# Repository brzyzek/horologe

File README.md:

# horologe
A watch utilizing an ESP32 processor.

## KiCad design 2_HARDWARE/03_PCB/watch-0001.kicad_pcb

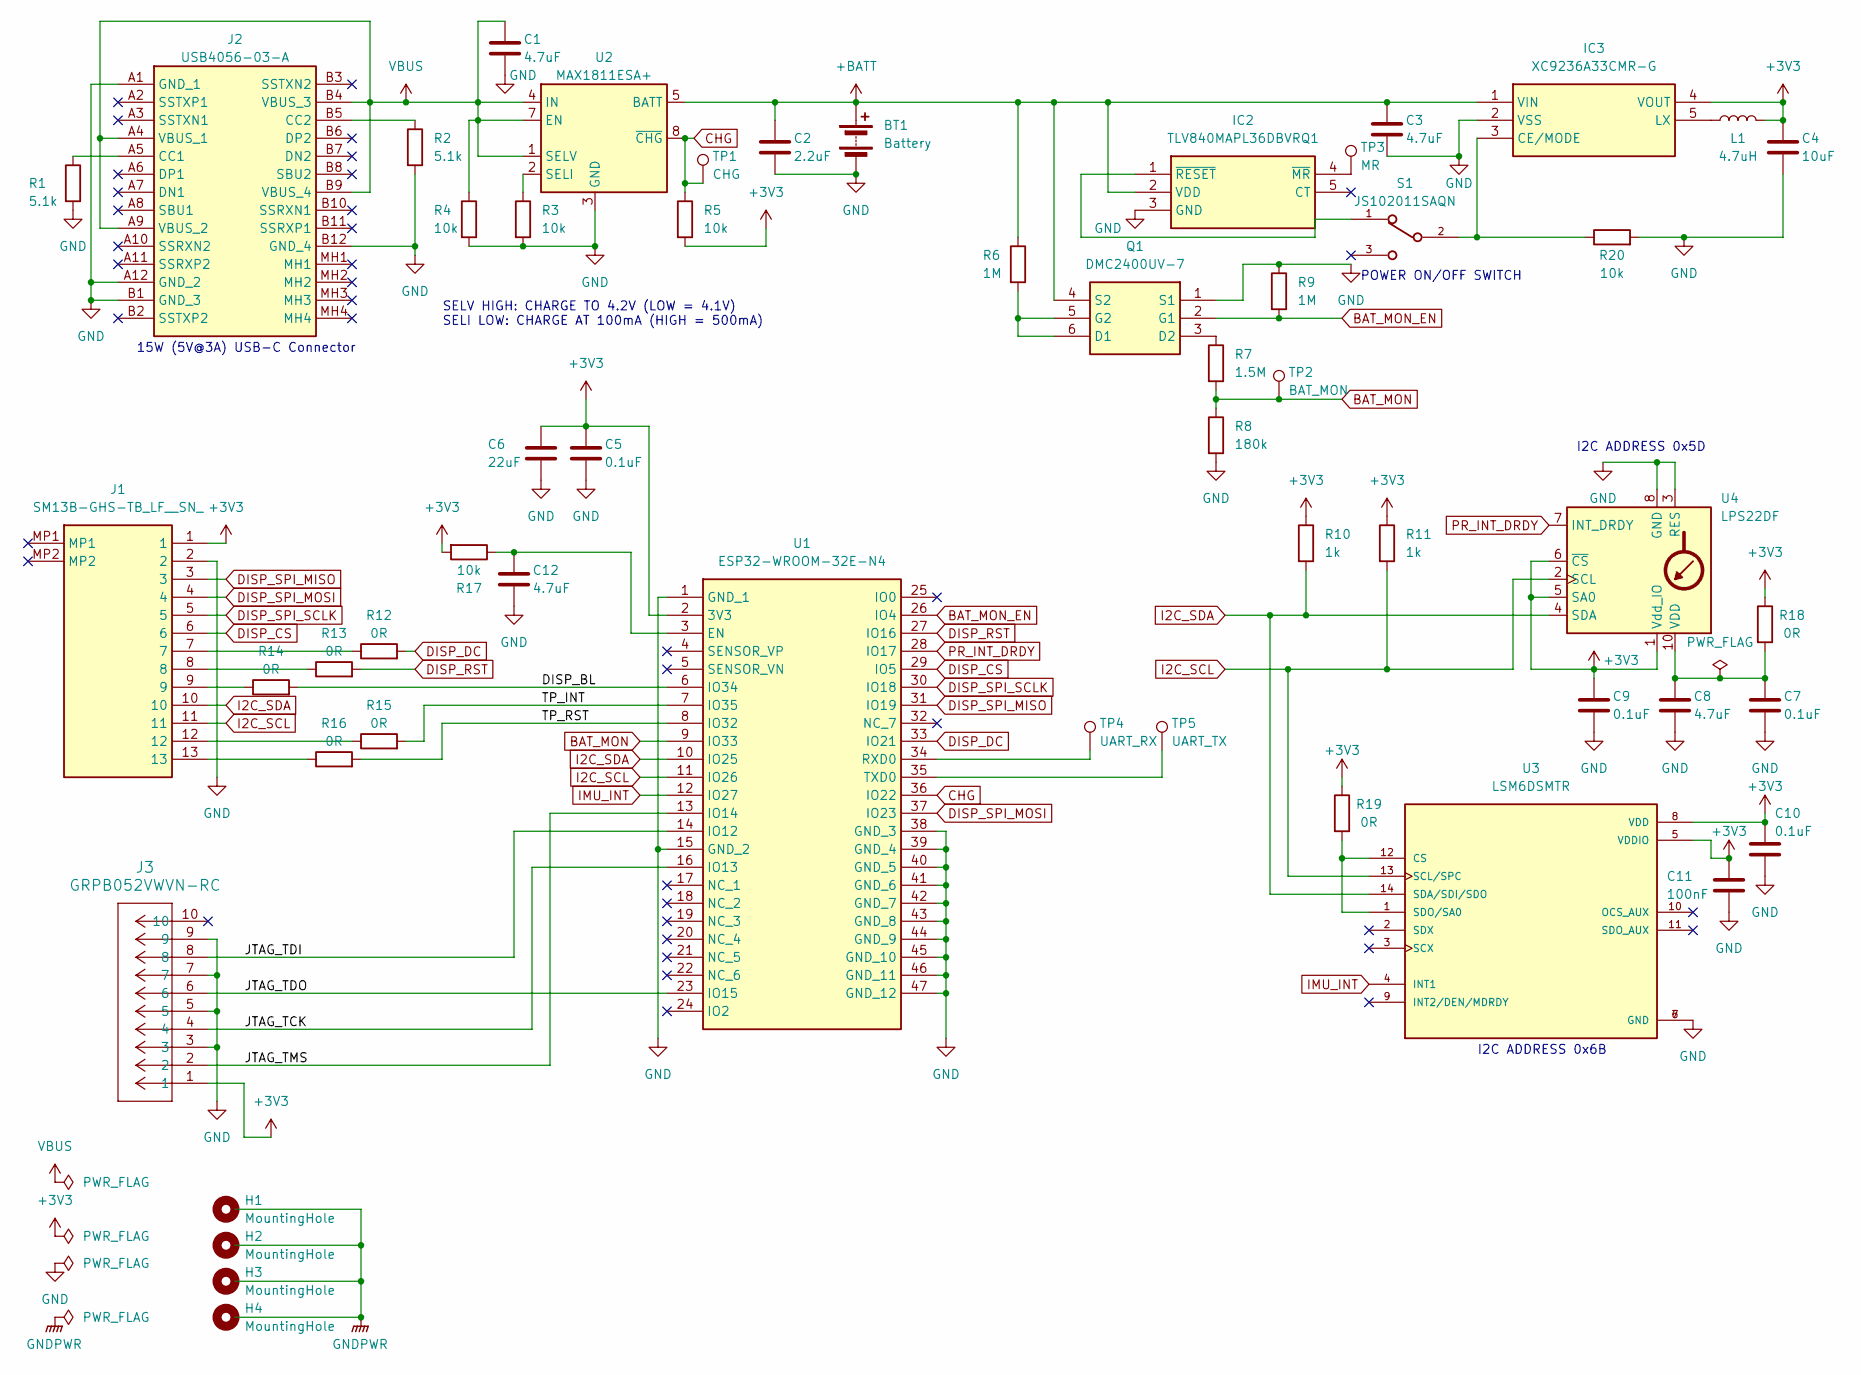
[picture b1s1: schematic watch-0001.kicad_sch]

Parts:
BT1: Battery; BAT_DUAL_1MM_TESTPOINTS
C1, C3, C8, C12: 4.7uF; C_0805_2012Metric
C2: 2.2uF; C_0805_2012Metric
C4: 10uF; C_0805_2012Metric
C5, C7, C9, C10: 0.1uF; C_0805_2012Metric
C6: 22uF; C_0805_2012Metric
C11: 100nF; C_0805_2012Metric
H1, H2, H3, H4: MountingHole; MountingHole_2.2mm_M2_DIN965_Pad
IC2: TLV840MAPL36DBVRQ1; SOT95P280X145-5N; Manufacturer_Part_Number TLV840MAPL36DBVRQ1; Mouser Part Number 595-V840MAPL36DBVRQ1
IC3: XC9236A33CMR-G; SOT95P280X130-5N; Manufacturer_Part_Number XC9236A33CMR-G; Mouser Part Number 865-XC9236A33CMR-G
J1: SM13B-GHS-TB_LF__SN_; SM13BGHSTBLFSN; Manufacturer_Part_Number SM13B-GHS-TB(LF)(SN)
J2: USB4056-03-A; USB405603A; Manufacturer_Part_Number USB4056-03-A; Mouser Part Number 640-USB4056-03-A
J3: GRPB052VWVN-RC; CONN_GRPB052VWVN-RC_SUL
L1: 4.7uH; IND_TAIYO_NR4018_TAY
Q1: DMC2400UV-7; SOTFL50P162X60-6N; Manufacturer_Part_Number DMC2400UV-7; Mouser Part Number 621-DMC2400UV-7
R1, R2: 5.1k; R_0603_1608Metric
R3, R4, R5, R17, R20: 10k; R_0603_1608Metric
R6, R9: 1M; R_0603_1608Metric
R7: 1.5M; R_0603_1608Metric
R8: 180k; R_0603_1608Metric
R10, R11: 1k; R_0603_1608Metric
R12, R13, R14, R15, R16, R18, R19: 0R; R_0603_1608Metric
S1: JS102011SAQN; SW_JS102011SAQN
TP1: CHG; TestPoint_Pad_D1.0mm
TP2: BAT_MON; TestPoint_Pad_D1.0mm
TP3: MR; TestPoint_Pad_D1.0mm
TP4: UART_RX; TestPoint_Pad_D1.0mm
TP5: UART_TX; TestPoint_Pad_D1.0mm
U1: ESP32-WROOM-32E-N4; ESP32WROOM32EN4; Manufacturer_Part_Number ESP32-WROOM-32E-N4; Mouser Part Number 356-ESP32WRM32E132PH
U2: MAX1811ESA+; SOIC-8_3.9x4.9mm_P1.27mm
U3: LSM6DSMTR; PQFN50P300X250X86-14N; PARTREV Rev 7
U4: LPS22DF; ST_HLGA-10_2x2mm_P0.5mm_LayoutBorder3x2y

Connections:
+3V3: C4.1, C5.1, C6.1, C9.1, C10.1, C11.1, IC3.4 (VOUT), J1.1, J3.1, L1.2, R5.2, R10.1, R11.1, R17.2, R18.1, R19.1, U1.2 (3V3), U3.5 (VDDIO), U3.8 (VDD), U4.1 (Vdd_IO), U4.5 (SA0), U4.6 (~CS)
+BATT: BT1.1 (+), C2.1, C3.1, IC2.2 (VDD), IC3.1 (VIN), Q1.4 (S2), R6.1, U2.5 (BATT)
/DISP_BL: R14.2, U1.6 (IO34)
/JTAG_TCK: J3.4, U1.16 (IO13)
/JTAG_TDI: J3.8, U1.14 (IO12)
/JTAG_TDO: J3.6, U1.23 (IO15)
/JTAG_TMS: J3.2, U1.13 (IO14)
/TP_INT: R15.2, U1.7 (IO35)
/TP_RST: R16.2, U1.8 (IO32)
BAT_MON: R7.2, R8.1, TP2.1, U1.9 (IO33)
BAT_MON_EN: Q1.2 (G1), R9.2, U1.26 (IO4)
CHG: R5.1, TP1.1, U1.36 (IO22), U2.8 (~CHG)
DISP_CS: J1.6, U1.29 (IO5)
DISP_DC: R12.2, U1.33 (IO21)
DISP_RST: R13.2, U1.27 (IO16)
DISP_SPI_MISO: J1.3, U1.31 (IO19)
DISP_SPI_MOSI: J1.4, U1.37 (IO23)
DISP_SPI_SCLK: J1.5, U1.30 (IO18)
GND: BT1.2 (-), C1.2, C2.2, C3.2, C4.2, C5.2, C6.2, C7.2, C8.2, C9.2, C10.2, C11.2, C12.2, IC2.3 (GND), IC3.2 (VSS), J1.2, J2.A1 (GND_1), J2.A12 (GND_2), J2.B1 (GND_3), J2.B12 (GND_4), J3.3, J3.5, J3.7, J3.9, Q1.1 (S1), R1.2, R2.2, R3.2, R4.2, R8.2, R9.1, R20.2, U1.1 (GND_1), U1.15 (GND_2), U1.38 (GND_3), U1.39 (GND_4), U1.40 (GND_5), U1.41 (GND_6), U1.42 (GND_7), U1.43 (GND_8), U1.44 (GND_9), U1.45 (GND_10), U1.46 (GND_11), U1.47 (GND_12), U2.3 (GND), U2.6 (GND), U3.6 (GND), U3.7 (GND), U4.3 (RES), U4.8 (GND), U4.9 (GND)
I2C_SCL: J1.11, R11.2, U1.11 (IO26), U3.13 (SCL/SPC), U4.2 (SCL)
I2C_SDA: J1.10, R10.2, U1.10 (IO25), U3.14 (SDA/SDI/SDO), U4.4 (SDA)
IMU_INT: U1.12 (IO27), U3.4 (INT1)
unnamed: IC2.4 (~MR), TP3.1
unnamed: IC2.1 (~RESET), S1.1
unnamed: IC3.3 (CE/MODE), R20.1, S1.2
unnamed: IC3.5 (LX), L1.1
unnamed: J1.7, R12.1
unnamed: J1.8, R13.1
unnamed: J1.9, R14.1
unnamed: J1.12, R15.1
unnamed: J1.13, R16.1
unnamed: J2.A5 (CC1), R1.1
unnamed: J2.B5 (CC2), R2.1
unnamed: Q1.5 (G2), Q1.6 (D1), R6.2
unnamed: Q1.3 (D2), R7.1
unnamed: C12.1, R17.1, U1.3 (EN)
unnamed: TP4.1, U1.34 (RXD0)
unnamed: TP5.1, U1.35 (TXD0)
unnamed: R3.1, U2.2 (SELI)
unnamed: R19.2, U3.1 (SDO/SA0), U3.12 (CS)
unnamed: C7.1, C8.1, R18.2, U4.10 (VDD)
PR_INT_DRDY: U1.28 (IO17), U4.7 (INT_DRDY)
VBUS: C1.1, J2.A4 (VBUS_1), J2.A9 (VBUS_2), J2.B4 (VBUS_3), J2.B9 (VBUS_4), R4.1, U2.1 (SELV), U2.4 (IN), U2.7 (EN)

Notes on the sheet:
SELV HIGH: CHARGE TO 4.2V (LOW = 4.1V) SELI LOW: CHARGE AT 100mA (HIGH = 500mA)
I2C ADDRESS 0x5D
15W (5V@3A) USB-C Connector
POWER ON/OFF SWITCH
I2C ADDRESS 0x6B

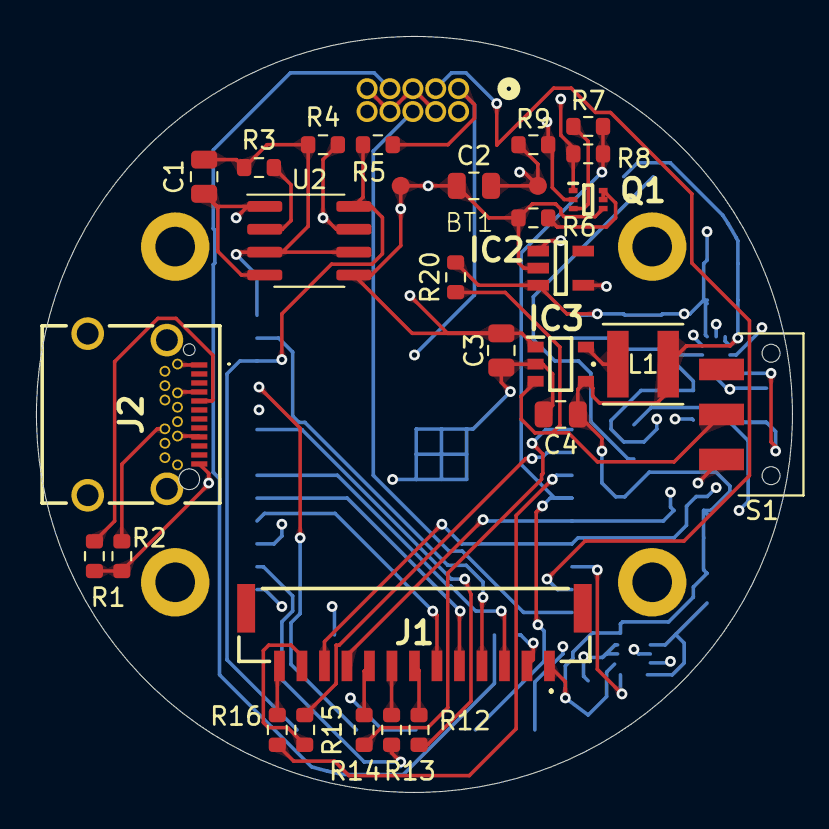
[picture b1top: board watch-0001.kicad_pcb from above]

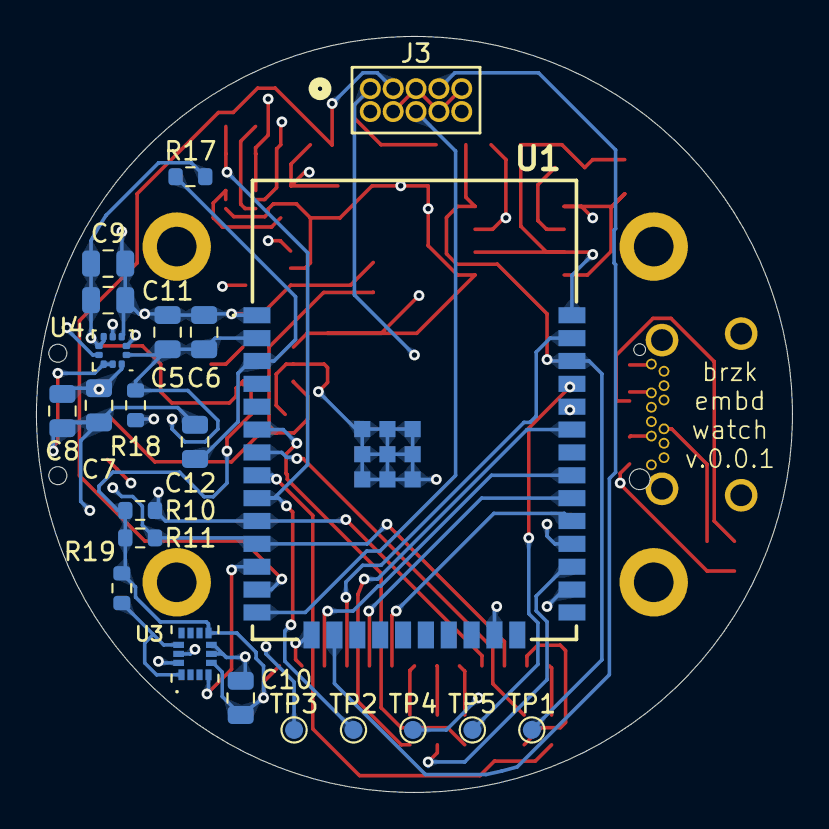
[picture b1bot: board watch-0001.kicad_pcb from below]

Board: 4 copper layers, 42.0 x 42.0 mm, 54 parts (22 on the bottom side), 43 nets.

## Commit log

2025-02-06 INIT
2025-02-06 INIT: Refactoring repositories.
2025-02-06 INIT: Initilizing .gitignore.
